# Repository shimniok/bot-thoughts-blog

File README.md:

# bot-thoughts-blog

A collection of example software from the [Bot Thoughts Blog](http://www.bot-thoughts.com)

* DayClock - firmware for an LED matrix clock that shows Day-of-Week and Time
* I2Cmaster - I2C Master for Parallax Propeller implemented to correctly use pull-down and recognize slave clock stretching
* Propeller - Using a Propeller for a vintage LED bubble display
* RPiTeleRover - web-based, tracked RaspberryPi Telepresence rover with cam and remote driving, includes sketchup drawings
* RS232toTTL - is an RS232-to-TTL voltage level-shifting circuit
* TBI	Initial revision	2 years ago
* TinySoftSerial - SoftwareSerial in C for ATtiny84A
* [TurntableStrobe](https://github.com/shimniok/TurntableStrobe) - a 50Hz/60Hz strobe to calibrate your turntable's speed, both handheld and module versions
* WebRinger - rings a bell whenever someone visits your website, using Raspberry Pi and Propeller.
* ledeyes	- ATtiny-based glowing, blinking LED eyes that you can add to your bushes at Halloween
* sobriety - JavaFX hackathon

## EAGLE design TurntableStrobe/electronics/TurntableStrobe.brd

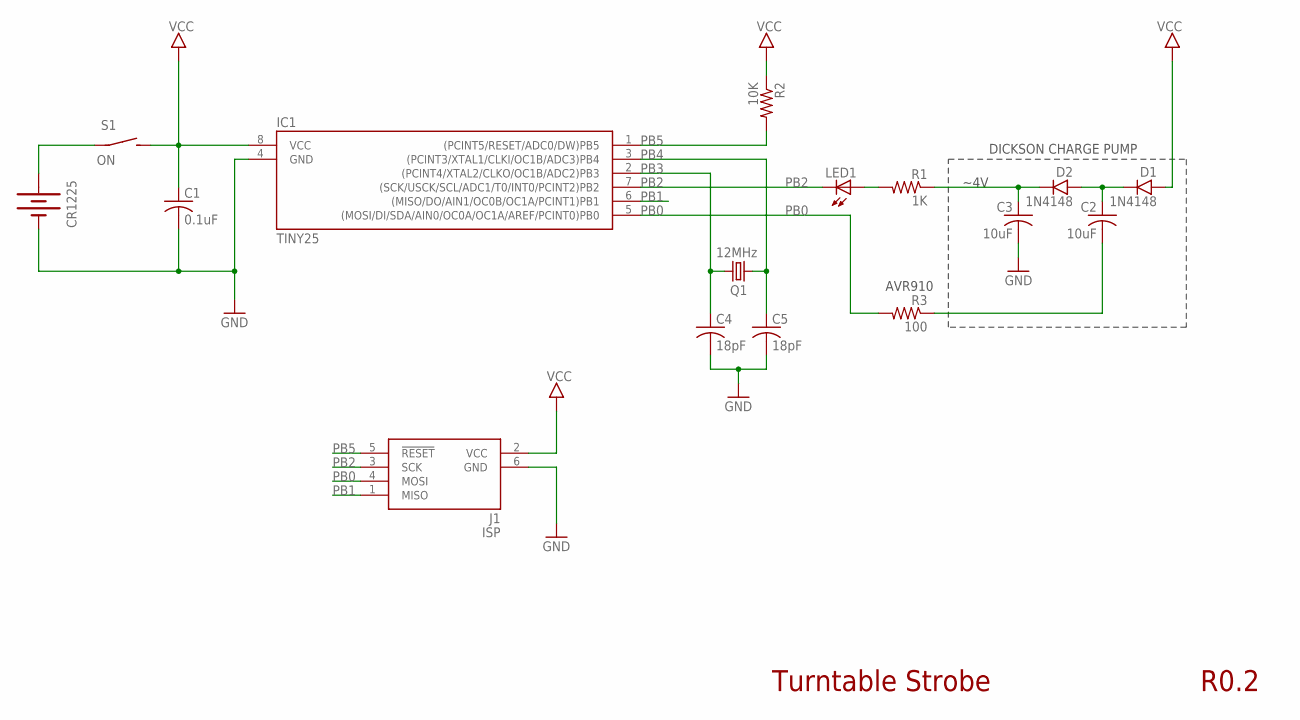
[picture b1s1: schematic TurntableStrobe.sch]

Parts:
C1: 0.1uF; C0603
C2, C3: 10uF; C0603
C4, C5: 18pF; C0603
CR1225: BATTERY12PTH; BATTCON_12MM_PTH
D1, D2: 1N4148; SOD-323
IC1: TINY25; SOIC8N
J1: ISP; 2X3_TP
LED1: LED5MMRA
Q1: 12MHz; NDK_2PAD_5X3
R1: 1K; R0603
R2: 10K; R0603
R3: 100; R0603
S1: ON; 6MMTACTILE_RECT

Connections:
GND: C1.2, C3.2, C4.2, C5.2, CR1225.GND (-), IC1.4 (GND), J1.6 (GND)
unnamed: C2.1, D1.C, D2.A
unnamed: LED1.A, R1.2
unnamed: C2.2, R3.1
PB0: IC1.5 ((MOSI/DI/SDA/AIN0/OC0A/OC1A/AREF/PCINT0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), J1.4 (MOSI), R3.2
PB1: IC1.6 ((MISO/DO/AIN1/OC0B/OC1A/PCINT1)PB1), J1.1 (MISO)
PB2: IC1.7 ((SCK/USCK/SCL/ADC1/T0/INT0/PCINT2)PB2), J1.3 (SCK), LED1.C
PB3: C4.1, IC1.2 ((PCINT4/XTAL2/CLKO/OC1B/ADC2)PB3), Q1.P$2 (2)
PB4: C5.1, IC1.3 ((PCINT3/XTAL1/CLKI/OC1B/ADC3)PB4), Q1.P$1 (1)
PB5: IC1.1 ((PCINT5/RESET/ADC0/DW)PB5), J1.5 (!RESET), R2.2
VBAT: CR1225.VCC@1 (+), S1.P$1
VCC: C1.1, D1.A, IC1.8 (VCC), J1.2 (VCC), R2.1, S1.P$2 (S)
VHI: C3.1, D2.C, R1.1

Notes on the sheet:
DICKSON CHARGE PUMP
~4V
AVR910
Turntable Strobe
R0.2

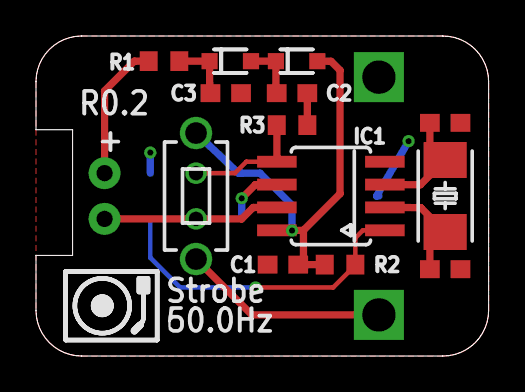
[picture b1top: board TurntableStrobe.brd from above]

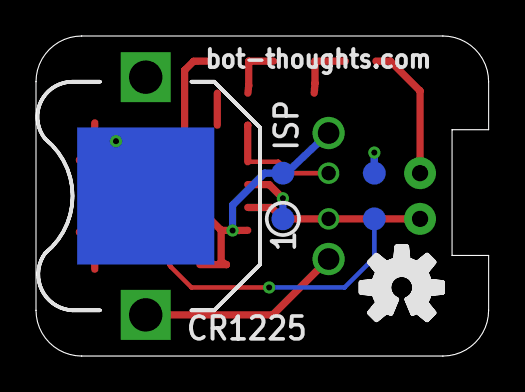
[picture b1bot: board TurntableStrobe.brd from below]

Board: 2 copper layers, 25.1 x 17.8 mm, 16 parts (2 on the bottom side), 13 nets.

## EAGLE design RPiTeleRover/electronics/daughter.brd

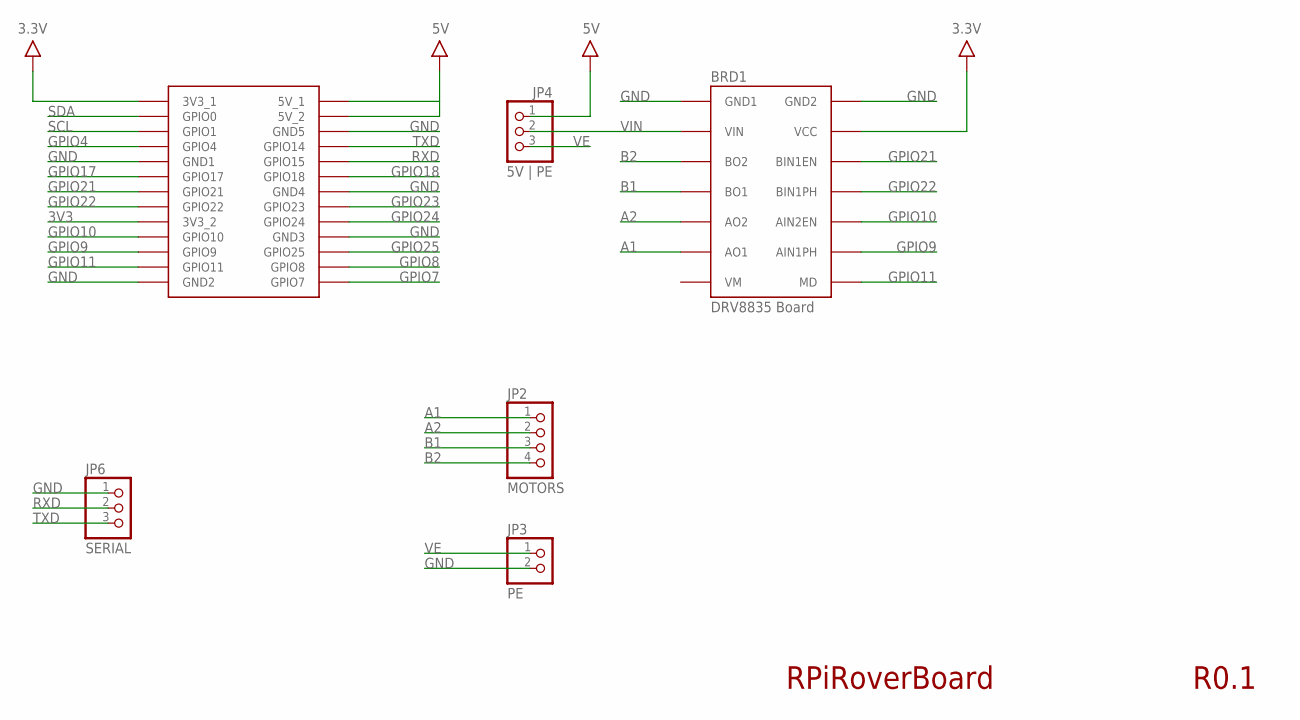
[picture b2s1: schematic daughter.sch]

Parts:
BRD1: DRV8835 Board; DRV8835BRD
JP1: RPI
JP2: MOTORS; 1X04-S
JP3: PE; 1X02-S
JP4: 5V | PE; 1X03-S
JP6: SERIAL; 1X03-S

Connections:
3.3V: BRD1.VCC, JP1.3V3_1
3V3: JP1.3V3_2
5V: JP1.5V_1, JP1.5V_2, JP4.1
A1: BRD1.AO1, JP2.1
A2: BRD1.AO2, JP2.2
B1: BRD1.BO1, JP2.3
B2: BRD1.BO2, JP2.4
GND: BRD1.GND1, BRD1.GND2, JP1.GND1, JP1.GND2, JP1.GND3, JP1.GND4, JP1.GND5, JP3.2, JP6.1
GPIO4: JP1.GPIO4
GPIO7: JP1.GPIO7
GPIO8: JP1.GPIO8
GPIO9: BRD1.AIN1PH, JP1.GPIO9
GPIO10: BRD1.AIN2EN, JP1.GPIO10
GPIO11: BRD1.MD, JP1.GPIO11
GPIO17: JP1.GPIO17
GPIO18: JP1.GPIO18
GPIO21: BRD1.BIN2EN (BIN1EN), JP1.GPIO21
GPIO22: BRD1.BIN1PH, JP1.GPIO22
GPIO23: JP1.GPIO23
GPIO24: JP1.GPIO24
GPIO25: JP1.GPIO25
RXD: JP1.GPIO15, JP6.2
SCL: JP1.GPIO1
SDA: JP1.GPIO0
TXD: JP1.GPIO14, JP6.3
VE: JP3.1, JP4.3
VIN: BRD1.VIN, JP4.2

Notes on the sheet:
RPiRoverBoard
R0.1

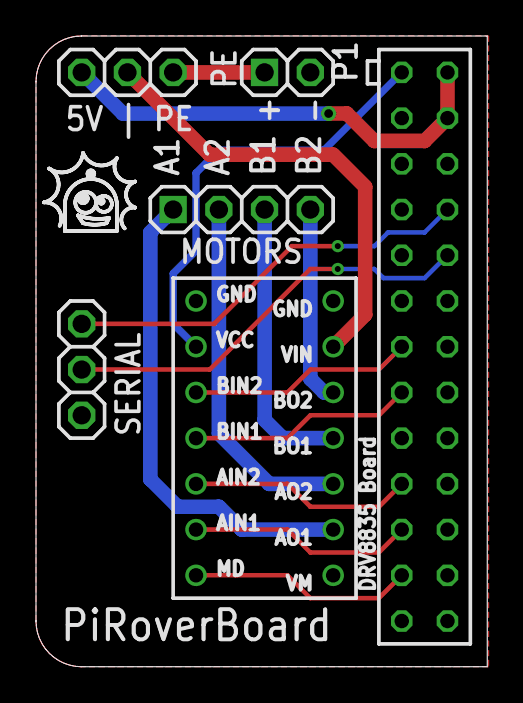
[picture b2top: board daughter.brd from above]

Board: 2 copper layers, 25.1 x 35.0 mm, 6 parts (0 on the bottom side), 16 nets.

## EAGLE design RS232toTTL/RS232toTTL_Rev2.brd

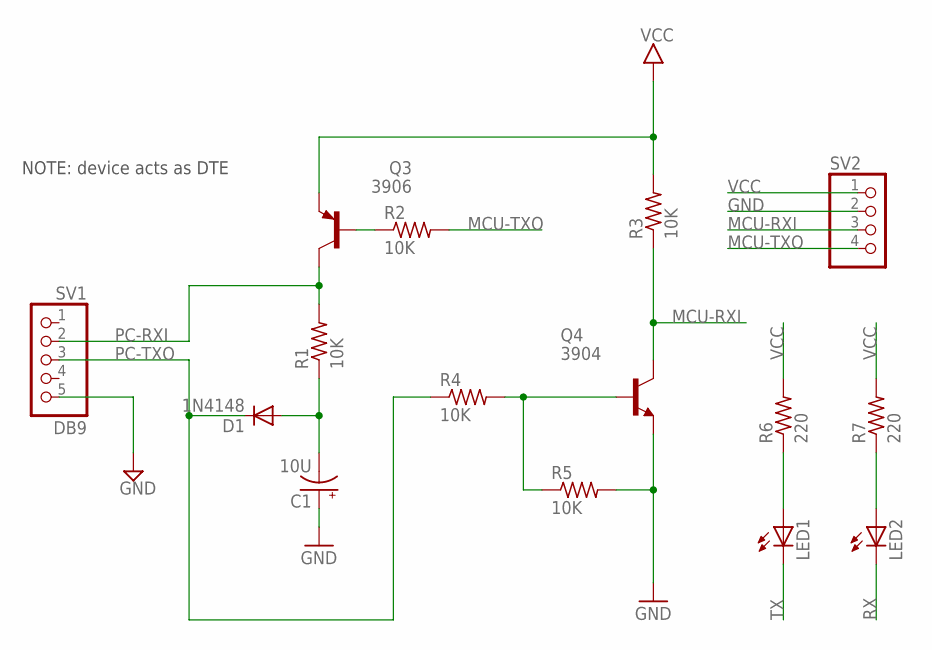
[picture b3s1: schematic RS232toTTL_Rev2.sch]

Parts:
C1: 10U; E2,5-5
D1: 1N4148; DO35-7
LED1, LED2: LED3MM
Q3: 3906; TO92-CBE
Q4: 3904; TO92-CBE
R1, R2, R3, R4, R5: 10K; 0204/5
R6, R7: 220; 0204/5
SV1: DB9; 1X05-S
SV2: PINHD-1X04_2.54-S; 1X04-S

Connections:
GND: C1.+, Q4.E, R5.2, SV1.5, SV2.2
MCU-RXI: Q4.C, R3.1, SV2.3
MCU-TXO: R2.2, SV2.4
unnamed: Q4.B, R4.2, R5.1
unnamed: Q3.B, R2.1
unnamed: LED1.A, R6.1
unnamed: C1.-, D1.A, R1.1
unnamed: LED2.A, R7.1
PC-RXI: Q3.C, R1.2, SV1.2
PC-TXO: D1.C, R4.1, SV1.3
RX: LED2.K (C)
TX: LED1.K (C)
VCC: Q3.E, R3.2, R6.2, R7.2, SV2.1

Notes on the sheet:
NOTE: device acts as DTE

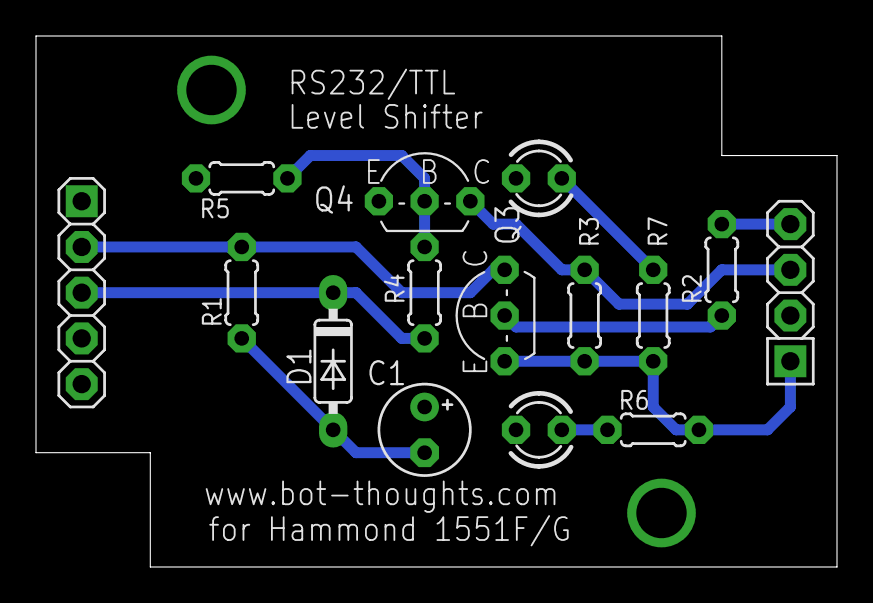
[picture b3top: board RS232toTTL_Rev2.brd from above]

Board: 2 copper layers, 44.5 x 29.5 mm, 15 parts (0 on the bottom side), 11 nets.

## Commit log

2011-11-10 Initial directory structure.
2011-11-10 Initial version
2011-11-10 Update for main blog
2013-04-04 New Project
2013-04-04 initial revision
2013-05-08 Added a folder to the repository for TBI
2013-05-24 Initial revision from blog plus revised version to fit enclosure.
2013-08-23 Initial folder
2013-08-23 Initial working version of I2Cmaster.spin with demo for HMC5843 magnetometer.
2013-08-23 Initial version of LG34200D.spin
2013-08-25 Updated comments
2013-08-27 Fixed bug with read; was off by 2 due to shift in the wrong spot.
2013-08-27 Initial revision of LSM303DLH.spin demo for compass/accel module from ST
2013-08-28 Updated significantly. Implemented 'buttons' disabling highlight for web browsers and iDevices. Auto-resizing attempt which sorta-works except on iPad. Separate css files and js files. Relying on jqu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
2013-08-28 Updated UI buttons to streamline code for button click management
2013-08-28 Fixed bug: hardcoded SDA/SCL pins. (me==dumbass)
2013-09-25 Initial
2013-09-25 Additional files
2013-09-25 Fixed broken references
2013-10-29 Moved web files into www directory. Added electronics directory. Added daughterboard card.
2013-10-29 Moving jquery.js into www
2013-11-01 LED glowing blinking eyes
2013-11-01 Added randomness to delays, # blinks, sleep seconds, inter-eye delay, etc.
2013-11-14 Initial version of SoftwareSerial in C for ATtiny84A
2014-01-15 New project: LED matrix clock that shows day of week
2014-01-15 Fixed bug at midnight, showing 0:00 instead of 12:00
2014-01-15 Minor font mods
2014-01-16 Font changes
2014-02-06 Updated comments with tips/warning on using slow clock and how to program chip in this situation.
2014-02-06 Added delay before slow_clock() in hopes that it'll permit the chip to be programmed at higher ISP frequency.
2014-02-07 Fixed startup delay to take 9.6MHz clock into account (64x faster)
2014-02-07 Removed extra routine. Why bother right? Just call delay(64000) up front.
2014-03-10 New project, TurntableStrobe
2014-03-10 Initial versions
2014-03-11 Clean up code.
2014-03-11 Fix for ISP (AVR910). Minor silk change.
2014-03-11 Revise diode footprint
2014-03-11 Clean up.
2014-03-11 Updated comments, more cleanup
2014-03-11 Change diode value to specify 1N4148
2014-03-18 Minor silk tweaks, firmware cleanup
2014-03-20 Revised to allow interactive time setting. Finished automatic Daylight Savings Time.
2014-03-20 Added SketchUp drawing
2014-03-31 Updated code, fixed timing issues. Timing is now showing 59.998950 Hz at 24MHz sampling on Saleae, which has accuracy of 24ns @ 12MHz sample rate.
2014-04-18 Fixed some JS stuff after updating webiopi library, converted rover.html to rover.php
2014-04-18 Switched back to rover.html, using javascript to pull hostname and dynamically loading image streaming Revised image sizing.
2014-04-18 Fixed image resizing, started to implement orientation handling.
2014-04-25 Module version of board.
2014-07-17 Fixed bug with missing MOSI.
2014-11-25 New directory
2014-11-25 Renaming to capture all my spin code.
2014-11-25 Updated loop now that I've fixed the bug with buffer overrun.
2014-11-25 Minor cleanup
2014-12-14 Modified code to compile 50, 60, 100, 120Hz versions
2015-03-10 Fixed DST bugs: blank hour display at h=0, incorrect time set during DST, incorrect time display during DST, etc.
2015-03-17 Removed hardware directory. Updated boards. Modified timing calcs spreadsheet.
2016-01-04 added char graphics into header
2016-01-04 moved dst calc into separate file
2016-01-04 moved serial i/o into separate file
2016-01-04 Moved drawing functions into separate file; added drawDate and drawMonth
2016-01-04 Moved various functions into separate files. Added month, date display.
2016-01-04 moved drawChar into separate file
2016-01-04 for DST: added spreadsheet to illustrate, added test harness for DST.ino
2016-01-04 moved date numerics/enums into separate header
2016-01-04 moved date enums to separate header, revised J char
2016-01-04 Revised and hopefully fixed DST computation
2016-01-04 changed arguments to dst routine
2016-01-06 minor update to spreadsheet

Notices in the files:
parts and their libraries:
SparkFun: Licensing: CC v3.0 Share-Alike You are welcome to use this library for commercial purposes.
